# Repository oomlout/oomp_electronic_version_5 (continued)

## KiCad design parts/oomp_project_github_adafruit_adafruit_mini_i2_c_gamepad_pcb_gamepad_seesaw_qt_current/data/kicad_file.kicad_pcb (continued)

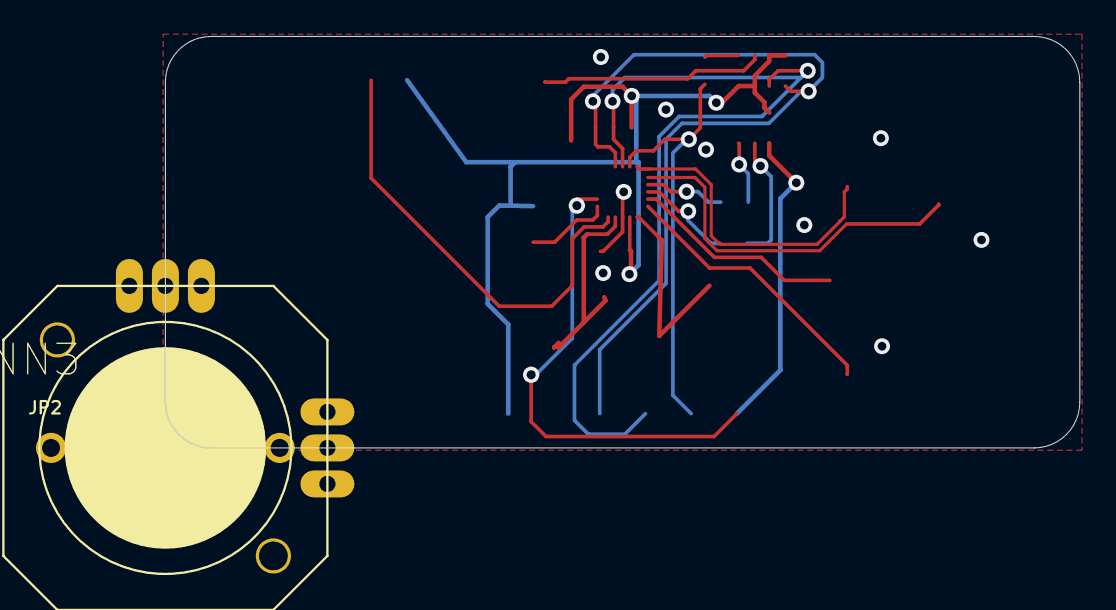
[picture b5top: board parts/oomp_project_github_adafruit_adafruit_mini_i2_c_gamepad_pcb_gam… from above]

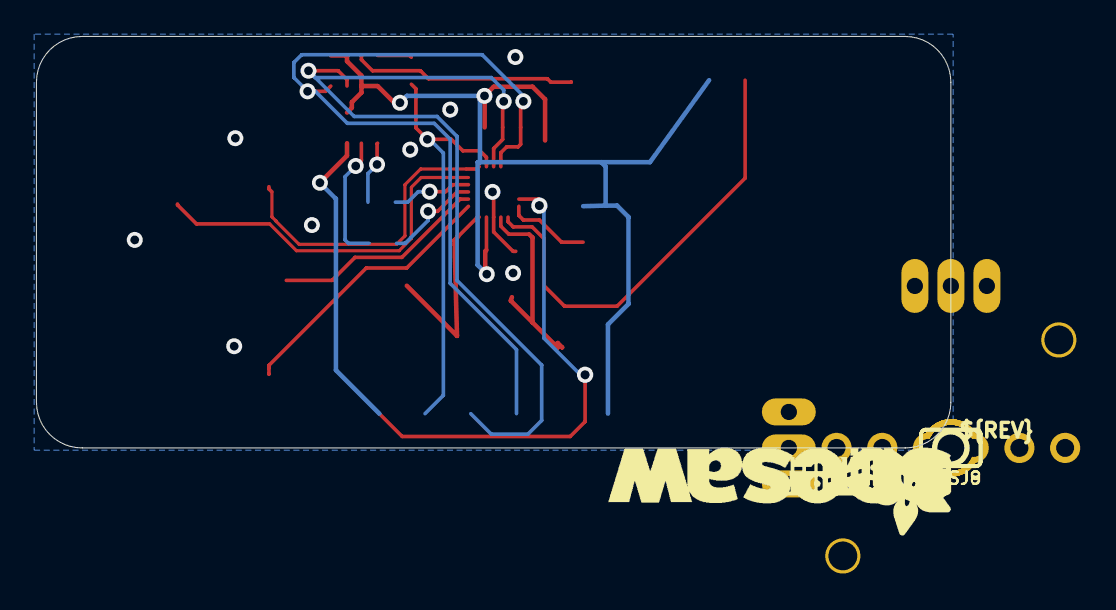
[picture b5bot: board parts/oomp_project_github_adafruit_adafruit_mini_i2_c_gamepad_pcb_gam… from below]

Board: 16 copper layers, 50.8 x 22.9 mm, 47 parts (16 on the bottom side), 20 nets.

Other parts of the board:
PLABEL0: PLABEL0
PLABEL1: PLABEL1
PLABEL2: PLABEL2
PLABEL3: PLABEL3
PLABEL4: PLABEL4
PLABEL5: PLABEL5
PLABEL6: PLABEL6
PLABEL7: PLABEL7
PLABEL8: PLABEL8
PLABEL9: PLABEL9
PLABEL10: PLABEL10
PLABEL11: PLABEL11
PLABEL12: PLABEL12
PLABEL13: PLABEL13
PLABEL14: PLABEL14
PLABEL15: PLABEL15
PLABEL16: PLABEL16
PLABEL17: PLABEL17
U$5: STEMMAQT
U$7: PCBFEAT-REV-040
U$9, U$11: ADAFRUIT_5MM
U$12: SEESAW_LOGO

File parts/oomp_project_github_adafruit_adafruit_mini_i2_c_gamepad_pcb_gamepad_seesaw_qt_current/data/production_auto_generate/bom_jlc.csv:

Comment,Designator,Footprint,LCSC Part #
,JP2,Gamepad Seesaw QT rev A-import-fps:1X06_ROUND,C37208
,"U$9,U$11",Gamepad Seesaw QT rev A-import-fps:ADAFRUIT_5MM,
,U$7,Gamepad Seesaw QT rev A-import-fps:PCBFEAT-REV-040,
,PLABEL0,Gamepad Seesaw QT rev A-import-fps:PLABEL0,
,PLABEL1,Gamepad Seesaw QT rev A-import-fps:PLABEL1,
,PLABEL10,Gamepad Seesaw QT rev A-import-fps:PLABEL10,
,PLABEL11,Gamepad Seesaw QT rev A-import-fps:PLABEL11,
,PLABEL12,Gamepad Seesaw QT rev A-import-fps:PLABEL12,
,PLABEL13,Gamepad Seesaw QT rev A-import-fps:PLABEL13,
,PLABEL14,Gamepad Seesaw QT rev A-import-fps:PLABEL14,
,PLABEL15,Gamepad Seesaw QT rev A-import-fps:PLABEL15,
,PLABEL16,Gamepad Seesaw QT rev A-import-fps:PLABEL16,
,PLABEL17,Gamepad Seesaw QT rev A-import-fps:PLABEL17,
,PLABEL2,Gamepad Seesaw QT rev A-import-fps:PLABEL2,
,PLABEL3,Gamepad Seesaw QT rev A-import-fps:PLABEL3,
,PLABEL4,Gamepad Seesaw QT rev A-import-fps:PLABEL4,
,PLABEL5,Gamepad Seesaw QT rev A-import-fps:PLABEL5,
,PLABEL6,Gamepad Seesaw QT rev A-import-fps:PLABEL6,
,PLABEL7,Gamepad Seesaw QT rev A-import-fps:PLABEL7,
,PLABEL8,Gamepad Seesaw QT rev A-import-fps:PLABEL8,
,PLABEL9,Gamepad Seesaw QT rev A-import-fps:PLABEL9,
,U$12,Gamepad Seesaw QT rev A-import-fps:SEESAW_LOGO,
,U$5,Gamepad Seesaw QT rev A-import-fps:STEMMAQT,
0.1uF,C5,Gamepad Seesaw QT rev A-import-fps:0603-NO,C14663
10K Pack,"R1,R6",Gamepad Seesaw QT rev A-import-fps:RESPACK_4X0603,C98220
10uF,C1,Gamepad Seesaw QT rev A-import-fps:0805-NO,
ATTINY8X6_QFN,X1,Gamepad Seesaw QT rev A-import-fps:QFN20_3MM,
GREEN,D3,Gamepad Seesaw QT rev A-import-fps:CHIPLED_0603_NOOUTLINE,
JOYSTICK_ANALOG_XY,JOY2,Gamepad Seesaw QT rev A-import-fps:JOYSTICK_ANALOG_MINITHM,
KMR2,"SW6,SW7",Gamepad Seesaw QT rev A-import-fps:BTN_RKB2_4.6X2.8,
Red,D4,Gamepad Seesaw QT rev A-import-fps:CHIPLED_0603_NOOUTLINE,
SJ_BUTTON,"SW1,SW2,SW3,SW4",Gamepad Seesaw QT rev A-import-fps:PUSHBUTTON_SMD_SJ,
STEMMA_I2C_QT,CONN3,Gamepad Seesaw QT rev A-import-fps:JST_SH4,C160404

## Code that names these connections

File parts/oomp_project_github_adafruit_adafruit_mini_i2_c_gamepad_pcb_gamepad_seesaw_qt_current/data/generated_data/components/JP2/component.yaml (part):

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        pin_name: '2'
      - reference: X1
        pin_number: '14'
        pin_name: PB0/SCL/TA.0/Y5/AIN11
    - number: '4'
      name: '4'
      electrical_type: passive
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        pin_name: '2'
      - reference: X1
        pin_number: '13'
        pin_name: PB1/SDA/TA.1/Y4/AIN0
    - number: '5'
      name: '5'
      electrical_type: passive
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        pin_name: C
      - reference: X1
        pin_number: '12'
        pin_name: PB2/TX/TA.2
    - number: '6'
      name: '6'
      electrical_type: passive
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        pin_name: '2'
      - reference: X1
        pin_number: '19'
        pin_name: PA0/UPDI/~{RESET}
    size:
      local_graphics:
        measurement: symbol graphics only; excludes pins, properties, and text
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    pin_name: '2'
  - reference: X1
    pin_number: '12'
    pin_name: PB2/TX/TA.2
  - reference: X1
    pin_number: '13'
    pin_name: PB1/SDA/TA.1/Y4/AIN0
  - reference: X1
    pin_number: '14'
    pin_name: PB0/SCL/TA.0/Y5/AIN11
  - reference: X1
    pin_number: '19'
    pin_name: PA0/UPDI/~{RESET}
  - reference: X1
    pin_number: '4'
    pin_name: VDD
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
